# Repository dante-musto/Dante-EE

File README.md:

# Smart-Watch
This project is meant to contain a MSP432, SSD1306, HC05 and a piezo buzzer. These files can be downloaded and edited to print different information
on the screen. Here is a pin map of how to connect the MSP

Board
Pin
Purpose

MSP432
1.6
SCL signal using I2C to control OLED Display
1.7
SDA signal using I2C to control OLED Display
3V3
Used to power DRV2605 on Group PCB
GND
Multiple GND pins - used to ground all boards
4.4
Enable for DRV2605L
6.0
Pin signal that all switches will use to control MSP432 - Will be a High signal for the MSP432
3.2
Input from PCB from buttons to control Modes
3.3
Input from PCB from buttons to control Modes
4.1
Input from PCB from buttons to control Modes
4.3
Input from PCB from buttons to control Modes
6.5
SDA signal using I2C to control DRV2605L
6.4
SCL signal using I2C to control DRV2605L
3V3
Powers Bluetooth module with 3.3V and 50mA
GND
Grounds Bluetooth module
2.5
TXD signal between MSP and HC-05
3.0
RXD signal between MSP and HC-05

SSD1306 OLED Display

VCC
Power from MSP432 3.3V
GND
Grounds OLED display
SCL
I2C communication with MSP432
SDA
I2C communication with MSP432

Datasheets

DRV2605L Datasheet
http://www.ti.com/lit/ds/symlink/drv2605l.pdf
MSP432 Technical Reference Manual
http://www.ti.com/lit/ug/slau356i/slau356i.pdf
HC05 Datasheet
http://www.electronicaestudio.com/docs/istd016A.pdf
SSD1306
https://cdn-shop.adafruit.com/datasheets/SSD1306.pdf

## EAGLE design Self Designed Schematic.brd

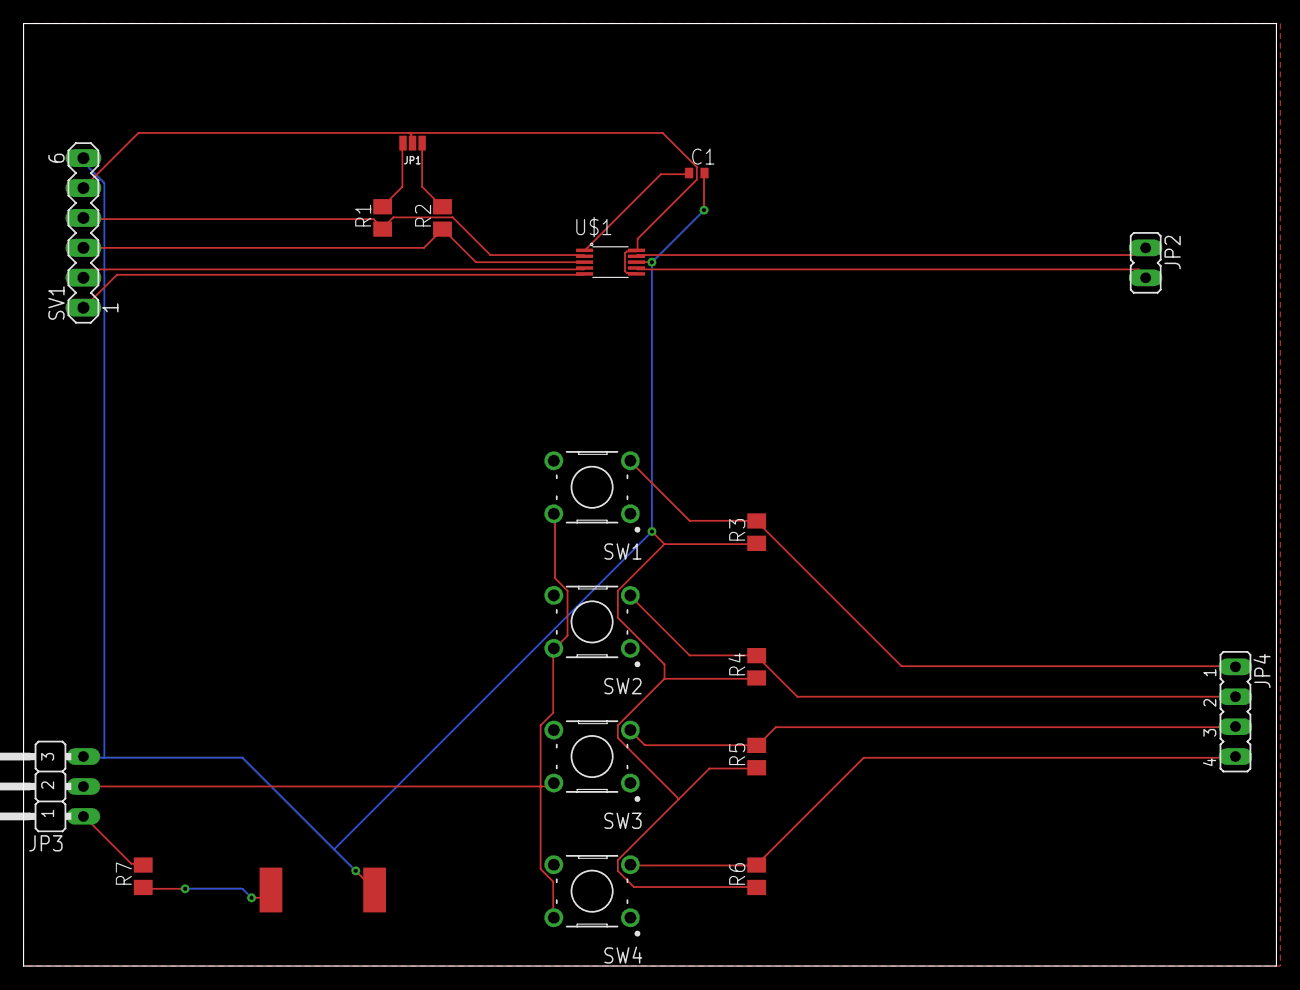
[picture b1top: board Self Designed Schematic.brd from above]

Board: 2 copper layers, 106.3 x 80.0 mm, 19 parts (0 on the bottom side), 18 nets.

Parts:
C1: C0402
JP1: JUMPER-SMT_3_2-NC_PASTE_NO-SILK; SMT-JUMPER_3_2-NC_PASTE_NO-SILK
JP2: JP1
JP3: JP2W
JP4: JP4
R1, R2, R3, R4, R5, R6, R7: M0805
SV1: MA06-1
SW1, SW2, SW3, SW4: B3F-1000
U$1: DRV2605L; VSSOP-10
U$2: PIEZOBUZZER

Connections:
GND: C1.2, JP3.3, R3.1, R4.1, R5.1, R6.1, SV1.6, U$1.P$8, U$2.P$2
unnamed: R1.1, SV1.4, U$1.P$2
unnamed: R2.1, SV1.3, U$1.P$3
unnamed: SV1.2, U$1.P$4
unnamed: SV1.1, U$1.P$5
unnamed: C1.1, U$1.P$1
unnamed: JP1.3, R1.2
unnamed: JP1.1, R2.2
unnamed: JP2.1, U$1.P$9
unnamed: JP2.2, U$1.P$7
unnamed: JP3.2, SW1.2, SW2.2, SW3.2, SW4.2
unnamed: JP4.4, R6.2, SW4.3
unnamed: JP4.3, R5.2, SW3.3
unnamed: JP4.2, R4.2, SW2.3
unnamed: JP4.1, R3.2, SW1.3
unnamed: JP3.1, R7.2
unnamed: R7.1, U$2.P$1
VCC: JP1.2, SV1.5, U$1.P$6, U$1.P$10

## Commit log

2019-12-15 Create README.md
    Here is the information for the user to use
2019-12-15 Update ssd1306.c
    Commented code

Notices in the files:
parts and their libraries:
SparkFun-Jumpers: Licensing: Creative Commons ShareAlike 4.0 International - https://creativecommons.org/licenses/by-sa/4.0
